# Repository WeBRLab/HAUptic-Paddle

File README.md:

# Haptic Paddle
<h2> This repository contains the design files and software for a single-DOF haptic display for STEM education.</h1>

<br/><br/><br/>
By: Auburn University Wearable and Bio-Robotics Lab <br/>
PI: **Chad G. Rose**  <br/>
Graduate Researchers: **Chandler Stubbs**, **Rhet Hailey**, **Avinash Baskaran**  <br/>
Undergraduate Researchers: **Zack Miller**, **Jamison Hood** <br/>

Instructions for flashing new code in Python:

1. Follow this tutorial to install micropython and configure micropython interpretter on logic board:
https://docs.sunfounder.com/projects/thales-kit/en/latest/micropython/python_start/install_micropython_to_pico.html

2. Run or Save your code on the RPI logic board as "main.py"

3. (optional) eject and re-insert USB cable to start code automatically.

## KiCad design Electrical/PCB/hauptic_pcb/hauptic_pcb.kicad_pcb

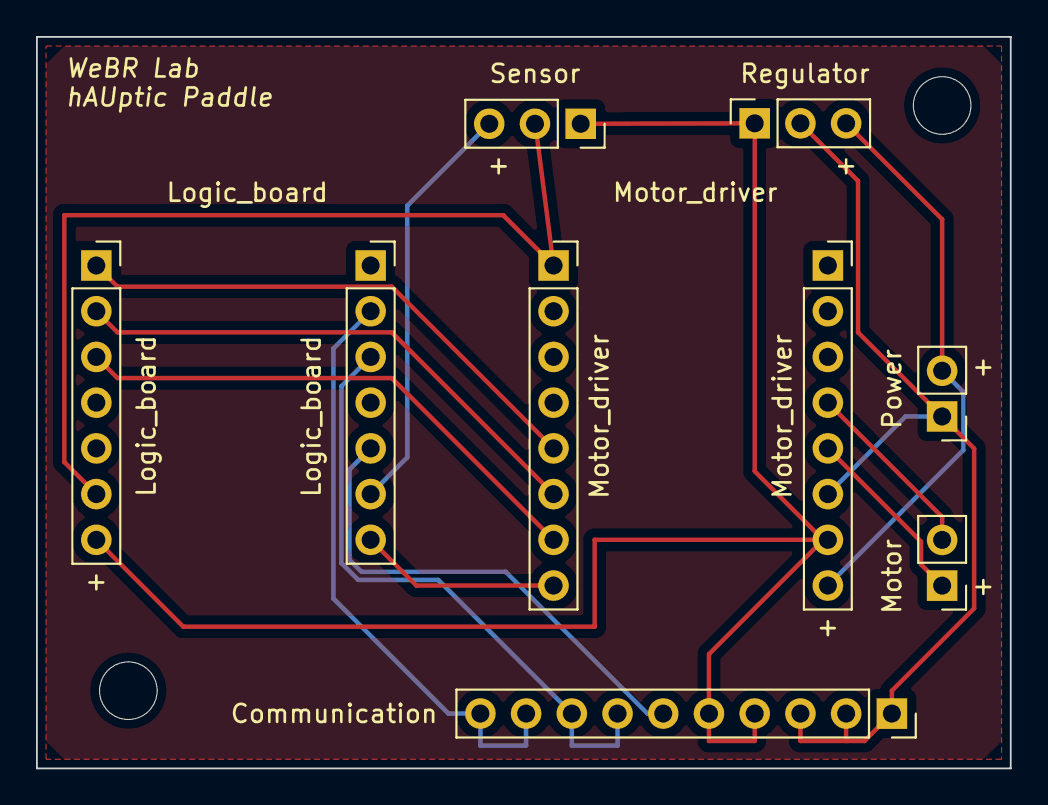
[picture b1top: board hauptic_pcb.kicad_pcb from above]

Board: 2 copper layers, 54.1 x 40.6 mm, 9 parts (0 on the bottom side), 14 nets.

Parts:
Communication: Conn_01x10_Female; PinSocket_1x10_P2.54mm_Vertical
Logic_board: Conn_01x07_Female; PinSocket_1x07_P2.54mm_Vertical
Logic_board#2: Conn_01x07_Female; PinSocket_1x07_P2.54mm_Vertical
Motor: Conn_01x02_Male; PinHeader_1x02_P2.54mm_Vertical
Motor_driver: Conn_01x08_Female; PinSocket_1x08_P2.54mm_Vertical
Motor_driver#2: Conn_01x08_Female; PinSocket_1x08_P2.54mm_Vertical
Power: Conn_01x02_Male; PinHeader_1x02_P2.54mm_Vertical
Regulator: Conn_01x03_Female; PinSocket_1x03_P2.54mm_Vertical
Sensor: Conn_01x03_Female; PinSocket_1x03_P2.54mm_Vertical

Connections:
unnamed: Communication.1, Communication.2, Communication.3, Motor_driver.6, Power.1, Regulator.2
unnamed: Communication.4, Communication.5, Logic_board#2.7, Motor_driver.7, Regulator.1, Sensor.1
unnamed: Communication.6, Logic_board.5
unnamed: Communication.7, Communication.8, Logic_board.3
unnamed: Communication.9, Communication.10, Logic_board.2
unnamed: Logic_board#2.1, Motor_driver#2.5
unnamed: Logic_board#2.2, Motor_driver#2.6
unnamed: Logic_board#2.3, Motor_driver#2.7
unnamed: Logic_board.7, Motor_driver#2.8
unnamed: Motor_driver.8, Power.2, Regulator.3
unnamed: Motor.2, Motor_driver.4
unnamed: Motor.1, Motor_driver.5
unnamed: Logic_board#2.6, Motor_driver#2.1, Sensor.2
unnamed: Logic_board.6, Sensor.3

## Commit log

2022-05-25 init
2022-05-25 cad update
2022-05-25 new CAD:
2022-05-25 Adding LFS.
2022-05-25 Added Adafruit ROB14450 motor driver library.
2022-05-25 Changed pico-sdk include path.
2022-05-25 first print
2022-05-26 uhhhhhhhh
2022-05-26 Added LCD library for Pi Pico.
2022-05-26 Changed motor mount to be adjustable. Added AU logo in haptic.
2022-05-26 sector pulley magnet slot
2022-05-26 Added test script for potentiometer in use with the UI.
2022-05-26 Added .gitignore
2022-05-26 Modified gitignore
2022-05-26 Housekeeping.
2022-05-27 linearizing sensor output for control
2022-05-27 descript
2022-05-31 allegro
2022-06-01 Made some changes to allegroMR library.
2022-06-09 allegro MR
2022-06-10 sensor linearization
2022-06-17 seeed rp2040 migration
2022-06-17 Reworked file structure towards a more finalized form.
2022-06-17 electrical
2022-06-17 Working on integrating Seeeduino RP2040 with motor driver.
2022-06-17 motor test
2022-06-17 some edits
2022-06-17 sensing
2022-06-28 hardware updates
2022-06-30 cad updates:
2022-07-27 controller instantiated and drafted
2022-09-22 committing
2022-11-15 printing update
2024-01-19 Add files via upload
    added motor plate .stl
2024-01-28 data-driven Control
2024-01-30 fra update
2024-11-13 Update LICENSE
2026-01-06 Create READ_ME
2026-01-07 Added Hardware File and Note
2026-01-07 Create Haptic Symposium Folder
2026-01-07 Create Note
2026-01-07 Create temp
2026-01-07 Added Solidworks Hardware Files
    Solidworks Files for Haptic Symposium Version of the hAUptic Paddle
2026-01-07 Added Assembly and Clean Up
    Removed a temp file
2026-01-07 Added BOM
2026-01-08 Added Calibration Setup
2026-01-08 Added DesiredPosition Sim
2026-01-08 Renamed Folder
2026-01-15 Adding Wifi Enabled stuff
